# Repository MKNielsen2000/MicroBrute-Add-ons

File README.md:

#Microbrute addon boards / hacks
---

A bunch of boards for hacking / modifying the MicroBrute:
* White Noise Add-on
* Buffered output add-on

**DISCLAIMER: These hacks/modifications are potentially dangerous for you and/or your synth. They are only for people with advanced electronics skills. I will not take any responsibility for any damage to your synth or yourself and understand that once you open your MicroBrute you lose your warranty.**

## White Noise Add-on
A tiny board that adds white noise to the Microbrute. 

Does what it says on the tin.

Based on a circuit from [Thomas Henry's noise generator cookbook](http://www.magsmoke.com/thomas_henry_books.asp).

Made possible thanks to [Yves Usson's publishing of all schematics related to the Microbrute.](http://hackabrute.yusynth.net/index_en.php)

#####STATUS
Boards done, need testing. 

####Connections

Power:
* Connect +12v to tp70 on the Microbrute
* Connect -12v to tp71 on the Microbrute
* Connect GND to tp72 on the Microbrute

White noise:
* Connect OUT on white noise board to tp47 (external audio in) on the Microbrute

## Buffered output Add-on
There are four waveform output hacks possible on the Microbrute but I've always thought it a damn shame that they get wired directly to output jacks with no protection and buffering which causes all sorts of issues. This boards fixes that problem. You mount this on one of the output jacks and wire three others to this board including the four waveforms. You can either pull the power from the above mentioned test points or daisy chain the power with the white noise generator. Pretty suave. 

#####STATUS
Boards done, need testing.

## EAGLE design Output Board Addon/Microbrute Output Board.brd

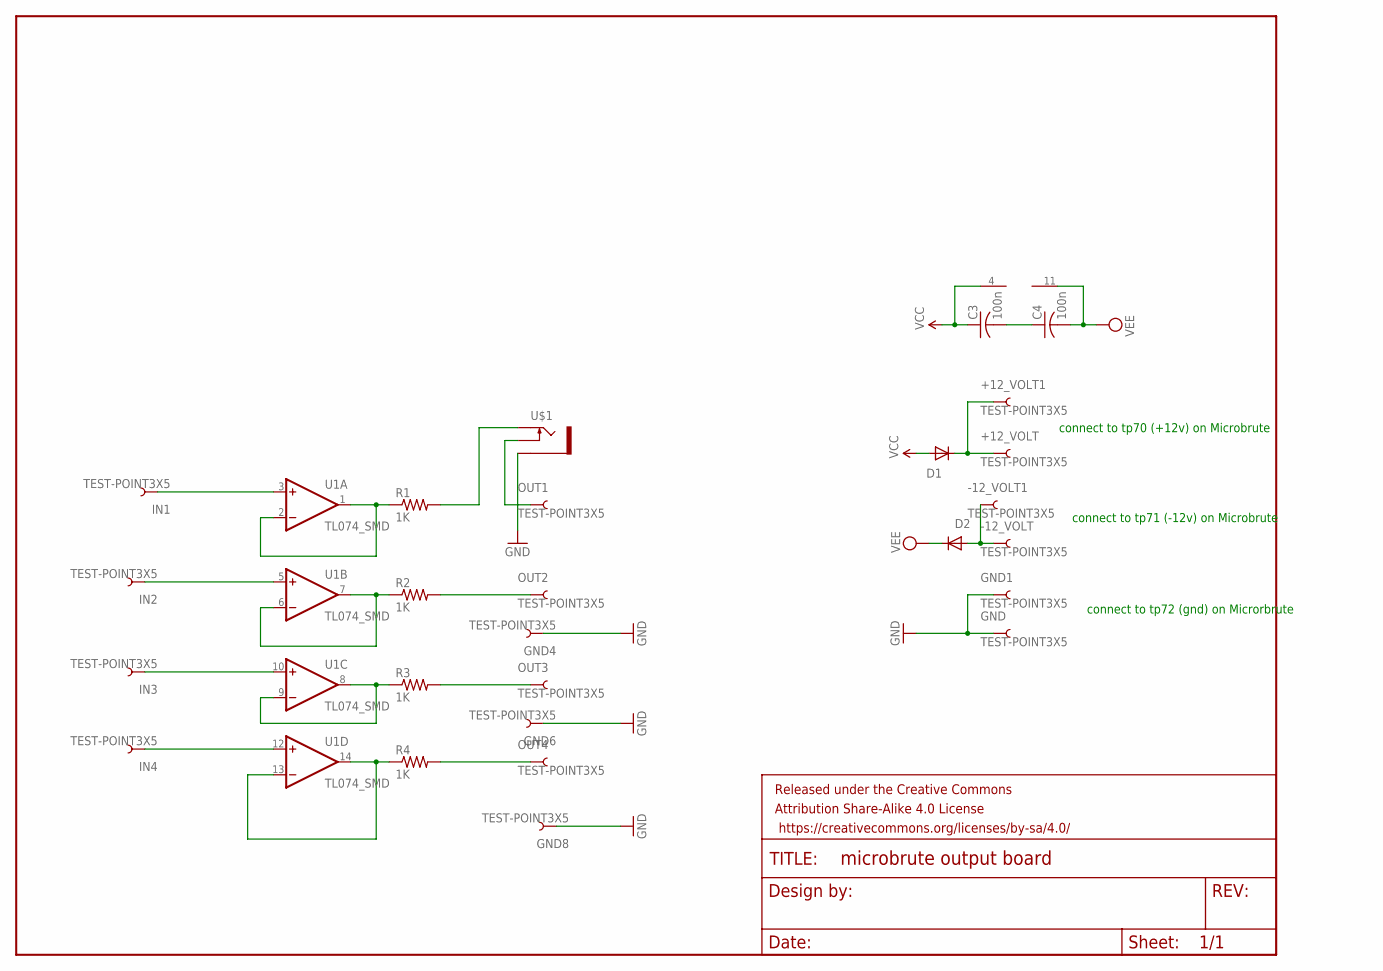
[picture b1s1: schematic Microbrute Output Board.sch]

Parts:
+12_VOLT, +12_VOLT1: TEST-POINT3X5; PAD.03X.05
-12_VOLT, -12_VOLT1: TEST-POINT3X5; PAD.03X.05
C3, C4: 100n; C0603
D1, D2: 1N5819HW; SOD123
FRAME1: FRAME-LETTER; CREATIVE_COMMONS
GND, GND1, GND4, GND6, GND8: TEST-POINT3X5; PAD.03X.05
IN1, IN2, IN3, IN4: TEST-POINT3X5; PAD.03X.05
OUT1, OUT2, OUT3, OUT4: TEST-POINT3X5; PAD.03X.05
R1, R2, R3, R4: 1K; 0603-RES
U1: TL074_SMD; SO14
U$1: THONKICONNNEW; WQP-PJ301M-12_JACK

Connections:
GND: GND.P$1, GND1.P$1, GND4.P$1, GND6.P$1, GND8.P$1, U$1.P$3_SLEEVE (SLEEVE)
GND1: C3.2, C4.1
unnamed: +12_VOLT.P$1, +12_VOLT1.P$1, D1.C
unnamed: -12_VOLT.P$1, -12_VOLT1.P$1, D2.A
unnamed: R1.2, U$1.P$1_TIP (TIP)
unnamed: OUT1.P$1, U$1.P$2_SWITCH (SWITCH)
unnamed: OUT2.P$1, R2.2
unnamed: R3.1, U1.8 (OUT), U1.9 (-IN)
unnamed: OUT4.P$1, R4.2
unnamed: R1.1, U1.1 (OUT), U1.2 (-IN)
unnamed: R2.1, U1.6 (-IN), U1.7 (OUT)
unnamed: OUT3.P$1, R3.2
unnamed: R4.1, U1.13 (-IN), U1.14 (OUT)
unnamed: IN2.P$1, U1.5 (+IN)
unnamed: IN3.P$1, U1.10 (+IN)
unnamed: IN4.P$1, U1.12 (+IN)
unnamed: IN1.P$1, U1.3 (+IN)
VCC: C3.1, D1.A, U1.4 (V+)
VEE: C4.2, D2.C, U1.11 (V-)

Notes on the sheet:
connect to tp70 (+12v) on Microbrute
connect to tp71 (-12v) on Microbrute
connect to tp72 (gnd) on Microrbrute

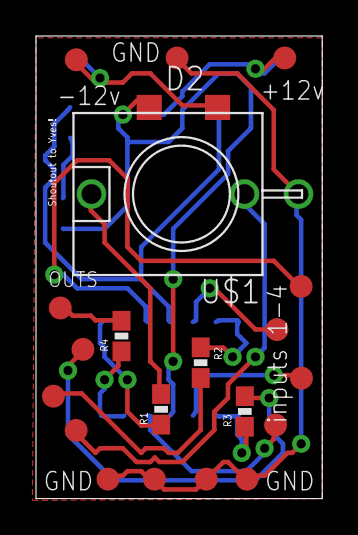
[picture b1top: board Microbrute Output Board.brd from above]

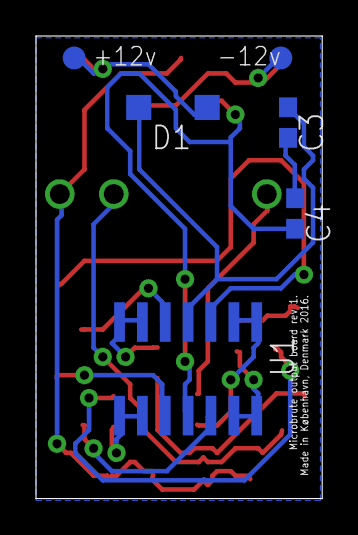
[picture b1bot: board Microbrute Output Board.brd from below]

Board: 2 copper layers, 15.9 x 25.7 mm, 28 parts (6 on the bottom side), 19 nets.

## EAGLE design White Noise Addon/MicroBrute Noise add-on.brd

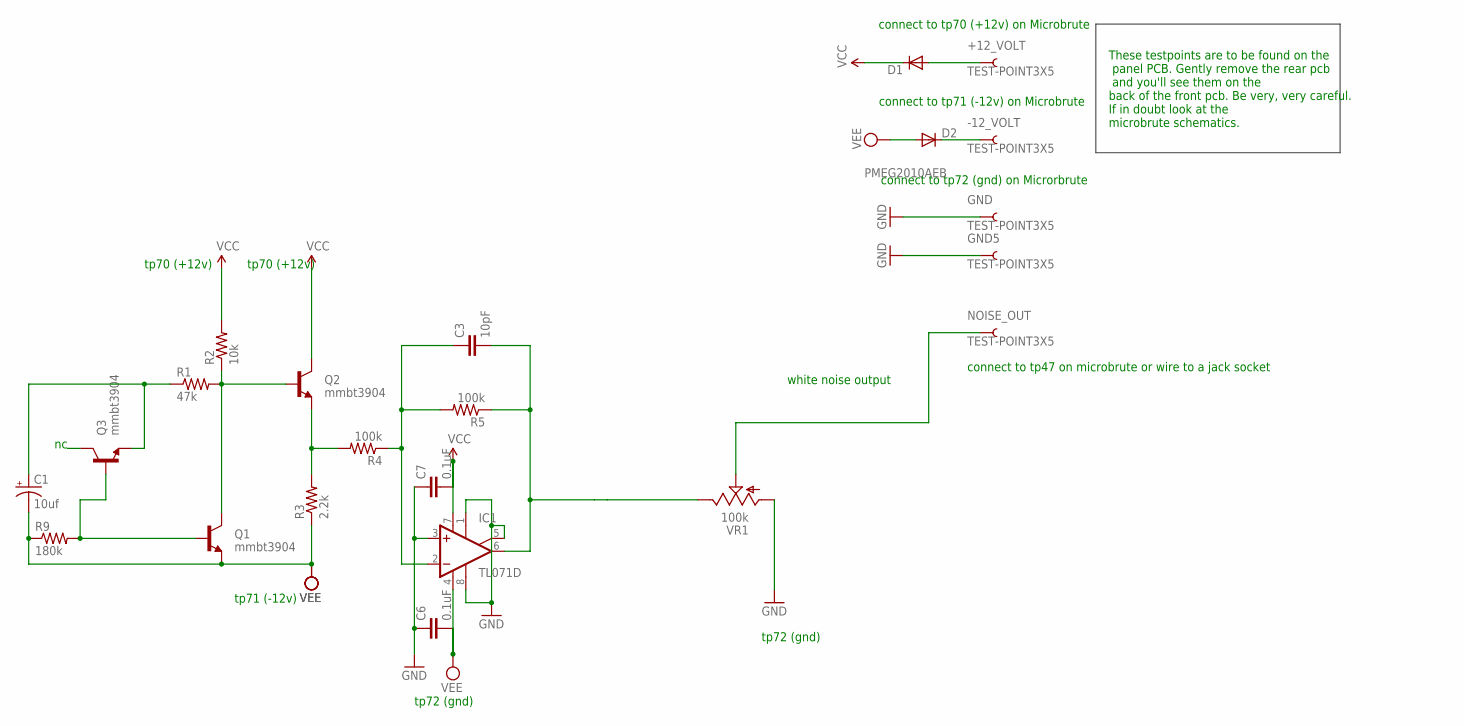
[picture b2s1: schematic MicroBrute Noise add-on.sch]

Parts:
+12_VOLT: TEST-POINT3X5; PAD.03X.05
-12_VOLT: TEST-POINT3X5; PAD.03X.05
C1: 10uf; PANASONIC_C
C3: 10pF; 0603-CAP
C6, C7: 0.1uF; 0603-CAP
D1, D2: PMEG2010AEB; SOD523
GND, GND5: TEST-POINT3X5; PAD.03X.05
IC1: TL071D; SO08
NOISE_OUT: TEST-POINT3X5; PAD.03X.05
Q1, Q2, Q3: mmbt3904; SOT23-3
R1: 47k; 0603-RES
R2: 10k; 0603-RES
R3: 2.2k; 0603-RES
R4, R5: 100k; 0603-RES
R9: 180k; 0603-RES
VR1: 100k; 9MM_SNAP-IN_POT

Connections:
GND: C6.1, C7.1, GND.P$1, GND5.P$1, IC1.1 (ON1), IC1.3 (+IN), IC1.5 (ON2), IC1.8 (OPT), VR1.1 (A)
unnamed: Q1.1 (B), Q3.1 (B), R9.2
unnamed: C1.+, Q3.2 (E), R1.1
unnamed: Q2.2 (E), R3.2, R4.2
unnamed: C3.2, IC1.6 (OUT), R5.1, VR1.3 (E)
unnamed: +12_VOLT.P$1, D1.A
unnamed: C3.1, IC1.2 (-IN), R4.1, R5.2
unnamed: -12_VOLT.P$1, D2.C
unnamed: Q1.3 (C), Q2.1 (B), R1.2, R2.1
unnamed: NOISE_OUT.P$1, VR1.2 (S)
VCC: C7.2, D1.C, IC1.7 (V+), Q2.3 (C), R2.2
VEE: C1.-, C6.2, D2.A, IC1.4 (V-), Q1.2 (E), R3.1, R9.1

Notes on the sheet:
tp71 (-12v)
tp70 (+12v)
tp72 (gnd)
white noise output
connect to tp70 (+12v) on Microbrute
connect to tp71 (-12v) on Microbrute
connect to tp72 (gnd) on Microrbrute
connect to tp47 on microbrute or wire to a jack socket
These testpoints are to be found on the panel PCB. Gently remove the rear pcb and you'll see them on the back of the front pcb. Be very, very careful. If in doubt look at the microbrute schematics.

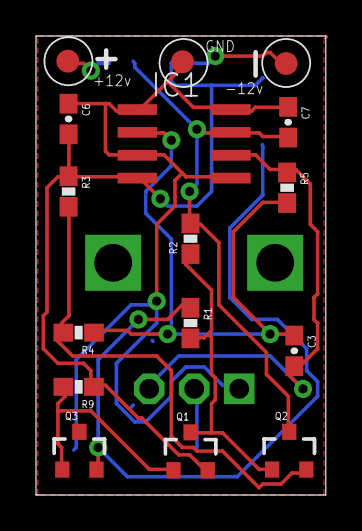
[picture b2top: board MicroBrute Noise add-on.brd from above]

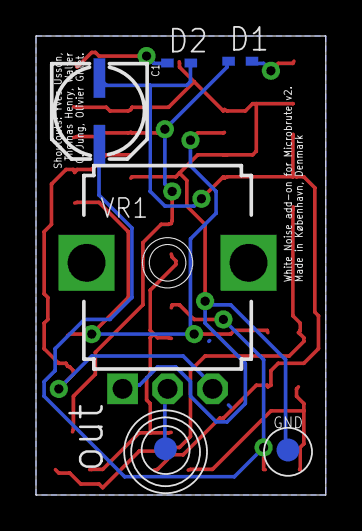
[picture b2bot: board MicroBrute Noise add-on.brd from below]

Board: 2 copper layers, 16.1 x 25.5 mm, 22 parts (6 on the bottom side), 12 nets.

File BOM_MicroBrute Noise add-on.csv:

"Part";"Value";"Device";"Package";"Description";"PROD_ID";"VALUE";
"+12_VOLT";"TEST-POINT3X5";"TEST-POINT3X5";"PAD.03X.05";"Bare copper test points for troubleshooting or ICT";"";"";
"-12_VOLT";"TEST-POINT3X5";"TEST-POINT3X5";"PAD.03X.05";"Bare copper test points for troubleshooting or ICT";"";"";
"C1";"10uf";"CAP_POLC";"PANASONIC_C";"Capacitor Polarized";"";"";
"C3";"10pF";"0.1UF-25V(+80/-20%)(0603)";"0603-CAP";"CAP-00810";"CAP-00810";"0.1uF";
"C6";"0.1uF";"0.1UF-25V(+80/-20%)(0603)";"0603-CAP";"CAP-00810";"CAP-00810";"0.1uF";
"C7";"0.1uF";"0.1UF-25V(+80/-20%)(0603)";"0603-CAP";"CAP-00810";"CAP-00810";"0.1uF";
"GND";"TEST-POINT3X5";"TEST-POINT3X5";"PAD.03X.05";"Bare copper test points for troubleshooting or ICT";"";"";
"IC1";"TL071D";"TL071D";"SO08";"OP AMP";"";"";
"NOISE_OUT";"TEST-POINT3X5";"TEST-POINT3X5";"PAD.03X.05";"Bare copper test points for troubleshooting or ICT";"";"";
"Q1";"mmbt3904";"TRANSISTOR_NPNSOT23-3";"SOT23-3";"Generic NPN BJT";"TRANS-08049";"";
"Q2";"mmbt3904";"TRANSISTOR_NPNSOT23-3";"SOT23-3";"Generic NPN BJT";"TRANS-08049";"";
"Q3";"mmbt3904";"TRANSISTOR_NPNSOT23-3";"SOT23-3";"Generic NPN BJT";"TRANS-08049";"";
"R1";"47k";"RESISTOR0603-RES";"0603-RES";"Resistor";"";"";
"R2";"10k";"RESISTOR0603-RES";"0603-RES";"Resistor";"";"";
"R3";"2.2k";"RESISTOR0603-RES";"0603-RES";"Resistor";"";"";
"R4";"100k";"RESISTOR0603-RES";"0603-RES";"Resistor";"";"";
"R5";"100k";"RESISTOR0603-RES";"0603-RES";"Resistor";"";"";
"R9";"180k";"RESISTOR0603-RES";"0603-RES";"Resistor";"";"";
"VR1";"100k";"9MM_SNAP-IN_POT_";"9MM_SNAP-IN_POT";"9mm vertical snap-in pot, Alpha / Panasonic style";"";"";

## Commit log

2016-05-30 touchup
2016-05-30 status added
2016-05-30 update for oshpark
2016-05-30 image update
2016-05-30 bom upload
2016-06-14 Added diodes to pcb, uploaded BOM
2016-06-14 added pic of power connections
2016-06-14 added image of tp47
2016-06-14 cleanup
2016-06-14 ready update
2016-06-14 Finished output board
2016-07-15 Fixed vital problem: Orientation of power diodes was wrong
2016-07-15 fucking markdown

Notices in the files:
parts and their libraries:
SparkFun-Aesthetics: Licensing: Creative Commons ShareAlike 4.0 International - https://creativecommons.org/licenses/by-sa/4.0
SparkFun-Aesthetics: Released under the Creative Commons Attribution Share-Alike 4.0 License
SparkFun-Aesthetics: https://creativecommons.org/licenses/by-sa/4.0
